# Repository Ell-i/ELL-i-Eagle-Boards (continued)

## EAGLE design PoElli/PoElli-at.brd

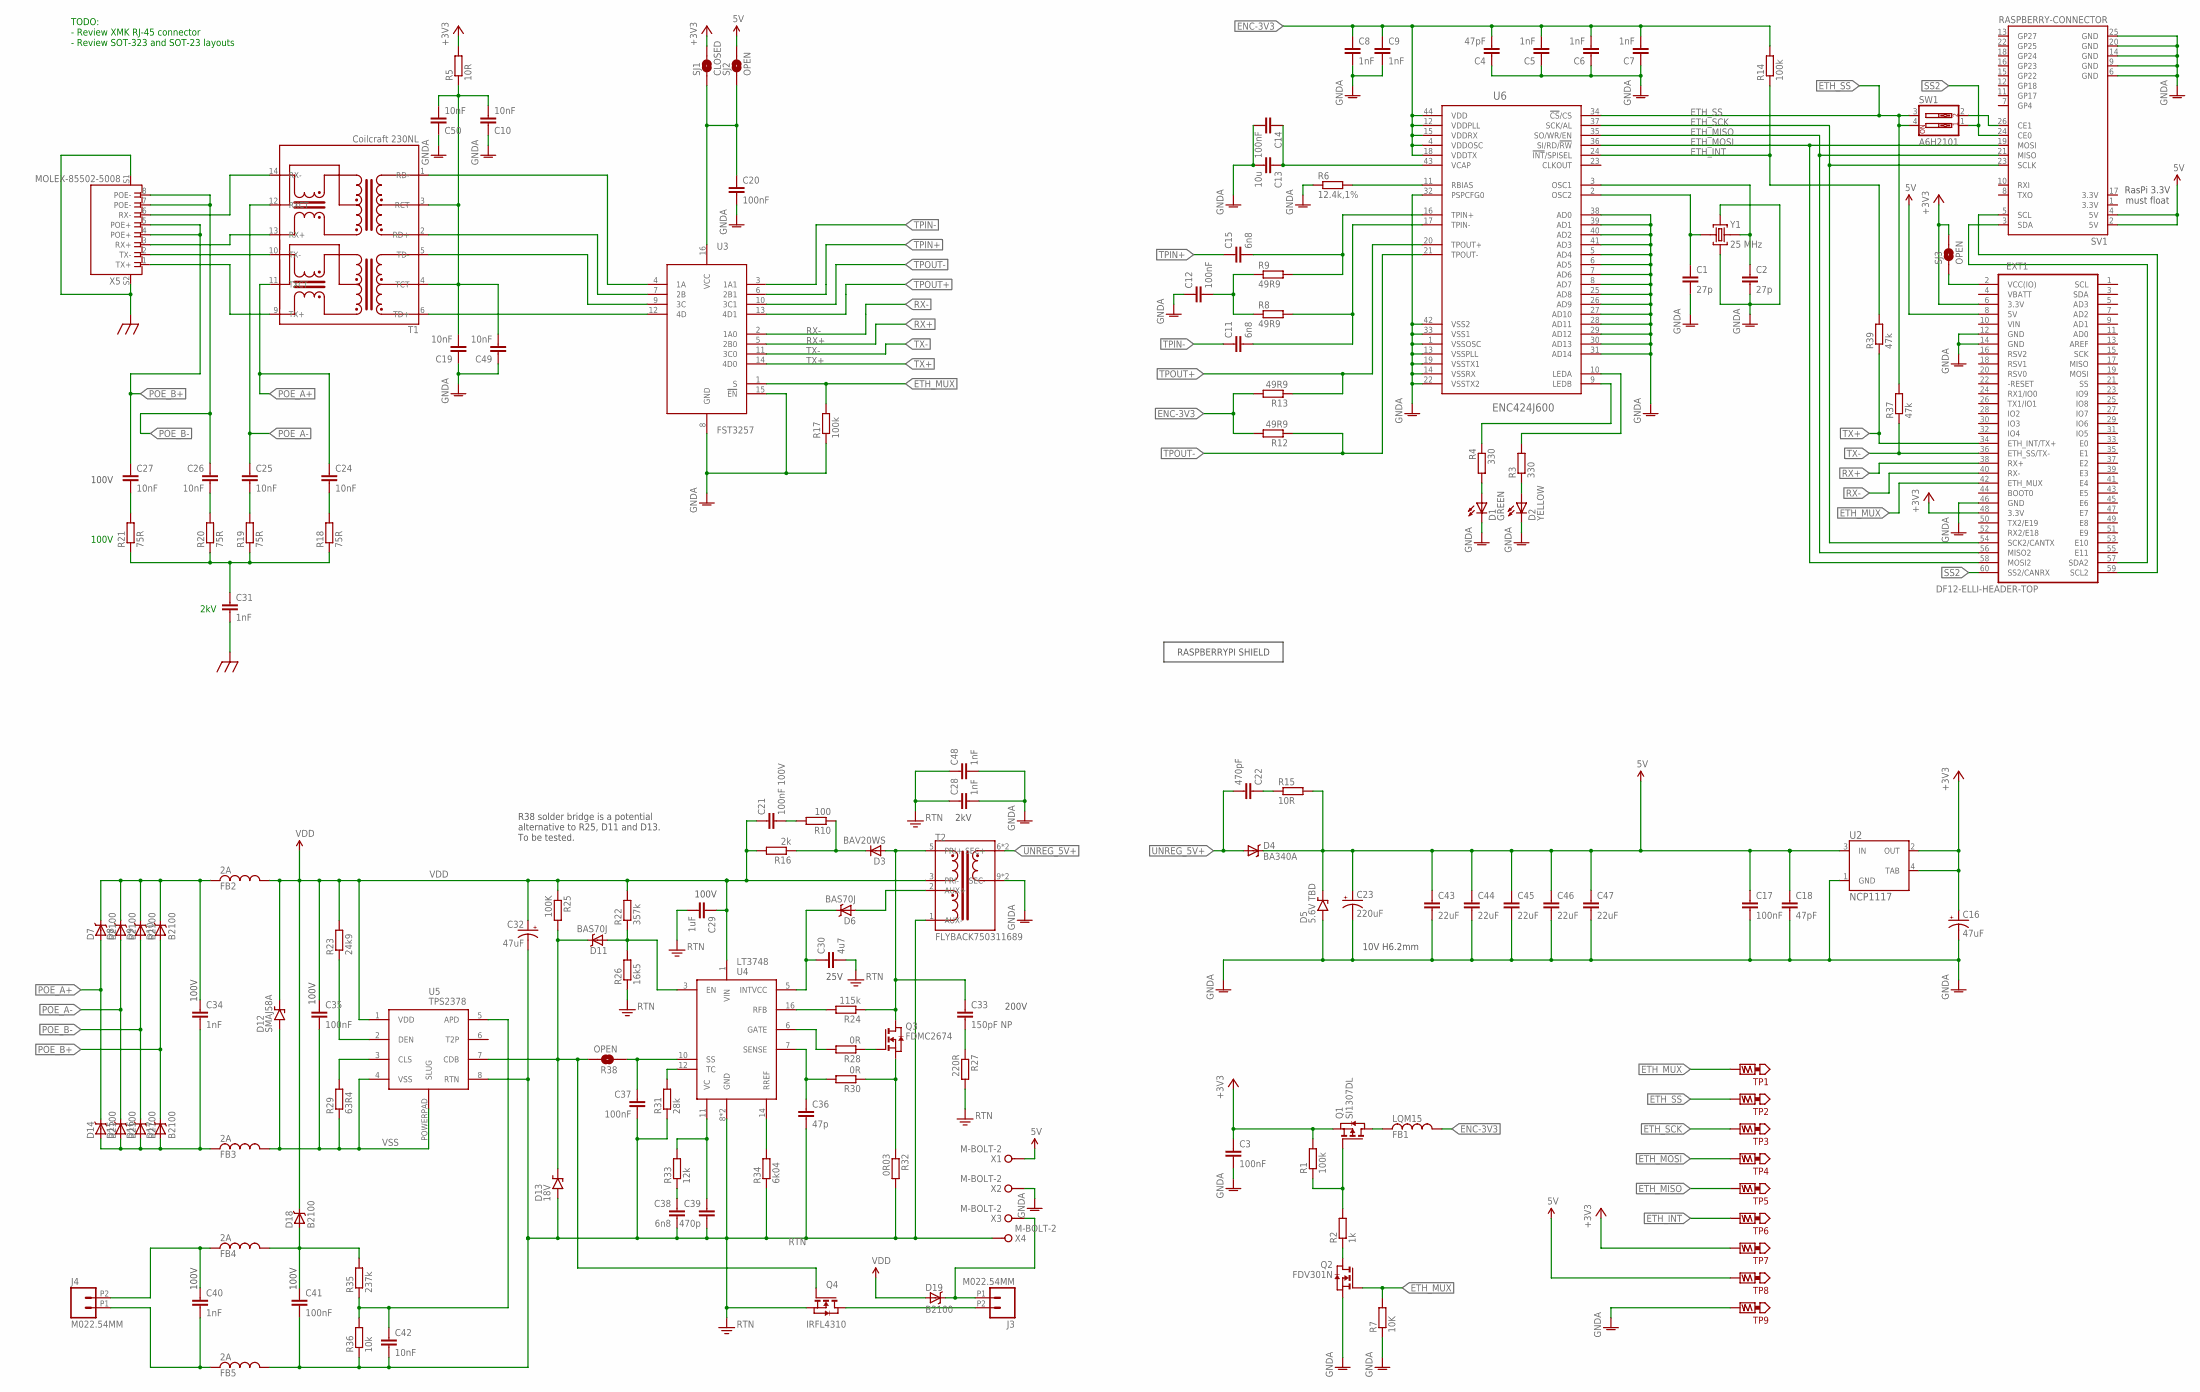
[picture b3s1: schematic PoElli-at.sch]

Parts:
C1, C2: 27p; C0402
C3, C12, C14, C17, C20, C37: 100nF; C0402
C4, C18: 47pF; C0402
C5, C6, C7, C8, C9: 1nF; C0402
C10, C19, C49, C50: 10nF; C0402
C11, C15, C38: 6n8; C0402
C13: 10u; C0603
C16, C32: 47uF; CT3216
C21: 100nF 100V; C0805
C22: 470pF; C0603
C23: 220uF; CPOL_PANASONIC_E
C24, C25, C26, C27, C42: 10nF; C0603
C28, C48: 1nF; C1206
C29: 1uF; C0805
C30: 4u7; C0805
C31: 1nF; C1210
C33: 150pF NP; C0805
C34, C40: 1nF; C0603
C35, C41: 100nF; C0805
C36: 47p; C0402
C39: 470p; C0402
C43, C44, C45, C46, C47: 22uF; C0805
D1: GREEN; LED-0603
D2: YELLOW; LED-0603
D3: BAV20WS; SOD-323
D4: BA340A; SMA-DIODE
D5: 5.6V TBD; SOD-123FL
D6, D11: BAS70J; SOD-323
D7, D8, D9, D10, D14, D15, D16, D17, D18, D19: B2100; DIODE-B2100
D12: SMAJ58A; SMA
D13: 18V; SOD-123FL
EXT1: DF12-ELLI-HEADER-TOP; DF12(4.0)-60DP-0.5V
FB1: LQM15; FB0402
FB2, FB3, FB4, FB5: 2A; FB1206
J3, J4: M022.54MM; 1X02_2.54_SCREWTERM
OUTLINE1: RASPBERRY-OUTLINE; RASPBERRYPI-SHIELD-OUTLINE
Q1: SI1307DL; SOT-323
Q2: FDV301N; SOT-23
Q3: FDMC2674; MLP8L33
Q4: IRFL4310; SOT223
R1, R14, R17: 100k; R0402
R2: 1k; R0402
R3, R4: 330; R0402
R5, R15: 10R; R0603
R6: 12.4k,1%; R0402
R7: 10K; R0402
R8, R9, R12, R13: 49R9; R0402
R10: 100; R0603
R16: 2k; R1206
R18, R19, R20, R21: 75R; R0603
R22: 357k; R0603
R23: 24k9; R0603
R24: 115k; R0603
R25: 100K; R0603
R26: 16k5; R0603
R27: 220R; R0805
R28, R30: 0R; R0603
R29: 63R4; R0805
R31: 28k; R0603
R32: 0R03; R0805
R33: 12k; R0603
R34: 6k04; R0603
R35: 237k; R0603
R36: 10k; R0603
R37, R39: 47k; R0805
R38: OPEN; SJ_2S-NO
SJ1: CLOSED; SJ_2S
SJ2, SJ3: OPEN; SJ_2S-NO
SV1: RASPBERRY-CONNECTOR; RASPBERRYPI-SHIELD-CONNECTOR
SW1: A6H2101; DIPSWITCH-02-50MIL
T1: Coilcraft 230NL; COILCRAFT-ETH1-230L
T2: FLYBACK750311689; WE_EP13_SMD_10PIN
TP1, TP5, TP6, TP7, TP8, TP9: TEST_POINT-5000; TP_5021
TP2, TP3, TP4: TEST_POINT-5021; TP_5000
U2: NCP1117; SOT223
U3: FST3257; SOIC-16-NARROW
U4: LT3748; MSOP16(12)
U5: TPS2378; SO08-POWERPAD
U6: ENC424J600; TQFP44-0.8MM
X1, X2, X3, X4: M-BOLT-2; M2-1
X5: MOLEX-85502-5008
Y1: 25 MHz; CRYSTAL-SMD-3225-GND

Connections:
3.3V: SV1.1 (3.3V), SV1.17 (3.3V)
5V: C17.1, C18.1, C23.+, C43.1, C44.1, C45.1, C46.1, C47.1, D4.C, D5.C, EXT1.8 (5V), R15.2, SJ2.2, SV1.2 (5V), SV1.4 (5V), TP8.P$1, U2.3 (IN), X1.1
+3V3: C3.1, C16.A (+), EXT1.6 (3.3V), EXT1.48 (3.3V), Q1.P$2 (S), R1.2, R5.2, SJ1.2, SJ3.2, TP7.P$1, U2.2 (OUT), U2.4 (TAB)
ENC-3V3: C4.2, C5.2, C6.2, C7.2, C8.1, C9.1, FB1.2, R12.2, R13.2, R14.2, U6.4 (VDDOSC), U6.12 (VDDPLL), U6.15 (VDDRX), U6.18 (VDDTX), U6.44 (VDD)
ETH_INT: R14.1, R39.2, TP6.P$1, U6.24 (!INT!/SPISEL)
ETH_MISO: EXT1.56 (MISO2), SV1.21 (MISO), TP5.P$1, U6.35 (SO/WR/EN)
ETH_MOSI: EXT1.58 (MOSI2), SV1.19 (MOSI), TP4.P$1, U6.36 (SI/RD/!RW)
ETH_MUX: EXT1.42 (ETH_MUX), Q2.P$1 (G), R7.2, R17.2, TP1.P$1, U3.1 (S)
ETH_SCK: EXT1.54 (SCK2/CANTX), SV1.23 (SCLK), TP3.P$1, U6.37 (SCK/AL)
ETH_SS: R37.2, SW1.3, SW1.4, TP2.P$1, U6.34 (!CS!/CS)
GNDA: C1.2, C2.2, C3.2, C4.1, C5.1, C6.1, C7.1, C8.2, C9.2, C10.1, C12.1, C13.2, C14.2, C16.C (-), C17.2, C18.2, C19.1, C20.2, C23.-, C28.2, C43.2, C44.2, C45.2, C46.2, C47.2, C48.2, C49.1, C50.1, D1.C, D2.C, D5.A, EXT1.12 (GND), EXT1.14 (GND), EXT1.46 (GND), Q2.P$2 (S), R6.1, R7.1, R17.1, SV1.6 (GND), SV1.9 (GND), SV1.14 (GND), SV1.20 (GND), SV1.25 (GND), T2.9 (SEC-), T2.10 (SEC-), TP9.P$1, U2.1 (GND), U3.8 (GND), U3.15 (!EN), U6.1 (VSSOSC), U6.5 (AD4), U6.6 (AD5), U6.7 (AD6), U6.8 (AD7), U6.13 (VSSPLL), U6.14 (VSSRX), U6.19 (VSSTX1), U6.22 (VSSTX2), U6.25 (AD8), U6.26 (AD9), U6.27 (AD10), U6.28 (AD11), U6.29 (AD12), U6.30 (AD13), U6.31 (AD14), U6.32 (PSPCFG0), U6.33 (VSS1), U6.38 (AD0), U6.39 (AD1), U6.40 (AD2), U6.41 (AD3), U6.42 (VSS2), X2.1, Y1.2 (GND), Y1.4 (GND)
unnamed: T1.10 (TX-), X5.2 (TX-)
unnamed: T1.9 (TX+), X5.1 (TX+)
unnamed: T1.13 (RX+), X5.3 (RX+)
unnamed: T1.14 (RX-), X5.6 (RX-)
unnamed: C31.1, R18.1, R19.1, R20.1, R21.1
unnamed: C34.1, D7.C, D8.C, D9.C, D10.C, FB2.1
unnamed: R31.2, U4.12 (TC)
unnamed: C34.2, D14.A, D15.A, D16.A, D17.A, FB3.1
unnamed: D11.2 (C), D13.C, Q4.1 (G), R25.2, R38.2, U5.7 (CDB)
unnamed: J3.P2 (2), Q4.2 (D), Q4.4 (D)
unnamed: T1.6 (TD+), U3.12 (4D)
unnamed: T1.5 (TD-), U3.9 (3C)
unnamed: T1.2 (RD+), U3.7 (2B)
unnamed: T1.1 (RD-), U3.4 (1A)
unnamed: C33.2, R27.1
unnamed: C22.1, R15.1
unnamed: D11.1 (A), R22.1, R26.2, U4.3 (EN)
unnamed: R23.1, U5.2 (DEN)
unnamed: R29.2, U5.3 (CLS)
unnamed: C37.1, R38.1, U4.10 (SS)
unnamed: D19.C, J3.P1 (1), X3.1
unnamed: C39.1, R33.2, U4.11 (VC)
unnamed: C38.1, R33.1
unnamed: R28.2, U4.6 (GATE)
unnamed: Q3.4 (G), R28.1
unnamed: C36.1, R30.2, U4.7 (SENSE)
unnamed: Q3.1 (S), Q3.2 (S), Q3.3 (S), R30.1, R32.1
unnamed: C33.1, D3.1 (A), Q3.5 (D), Q3.6 (D), Q3.7 (D), Q3.8 (D), Q3.F1 (D), R24.1, T2.5 (PRI+)
unnamed: D6.1 (A), T2.2 (AUX+)
unnamed: R24.2, U4.16 (RFB)
unnamed: R34.2, U4.14 (RREF)
unnamed: D3.2 (C), R10.1, R16.1
unnamed: C21.2, R10.2
unnamed: D1.A, R4.2
unnamed: C1.1, U6.2 (OSC2), Y1.1 (C1)
unnamed: D2.A, R3.1
unnamed: C11.2, R8.2, U6.17 (TPIN-)
unnamed: C10.2, C19.2, C49.2, C50.2, R5.1, T1.3 (RCT), T1.4 (TCT)
unnamed: R4.1, U6.9 (LEDB)
unnamed: R3.2, U6.10 (LEDA)
unnamed: C12.2, R8.1, R9.1
unnamed: R6.2, U6.11 (RBIAS)
unnamed: C2.1, U6.3 (OSC1), Y1.3 (C2)
unnamed: C27.2, R21.2
unnamed: C24.2, R18.2
unnamed: C25.2, R19.2
unnamed: C26.2, R20.2
unnamed: C40.1, FB4.1, J4.P2 (2)
unnamed: C42.1, R35.1, R36.2, U5.5 (APD)
unnamed: C40.2, FB5.1, J4.P1 (1)
unnamed: Q2.P$3 (D), R2.1
unnamed: Q1.P$1 (G), R1.1, R2.2
unnamed: C15.2, R9.2, U6.16 (TPIN+)
unnamed: FB1.1, Q1.P$3 (D)
unnamed: EXT1.57 (SDA2), SV1.3 (SDA)
unnamed: EXT1.59 (SCL2), SV1.5 (SCL)
unnamed: SV1.26 (CE1), SW1.2
unnamed: C41.1, D18.A, FB4.2, R35.2
POE_A+: C24.1, D7.A, D14.C, T1.11 (TXCT)
POE_A-: C25.1, D8.A, D15.C, T1.12 (RXCT)
POE_B+: C27.1, D10.A, D17.C, X5.4 (POE+), X5.5 (POE+)
POE_B-: C26.1, D9.A, D16.C, X5.7 (POE-), X5.8 (POE-)
RTN: C28.1, C29.2, C30.2, C32.C (-), C36.2, C37.2, C38.2, C39.2, C41.2, C42.2, C48.1, D13.A, FB5.2, Q4.3 (S), R26.1, R27.2, R31.1, R32.2, R34.1, R36.1, T2.1 (AUX-), U4.8 (GND), U4.9 (GND), U5.8 (RTN), X4.1
RX+: EXT1.38 (RX+), U3.5 (2B0)
RX-: EXT1.40 (RX-), U3.2 (1A0)
SGND: C31.2, X5.S1 (GND), X5.S2 (GND)
SS2: EXT1.60 (SS2/CANRX), SV1.24 (CE0), SW1.1
TPIN+: C15.1, U3.6 (2B1)
TPIN-: C11.1, U3.3 (1A1)
TPOUT+: R13.1, U3.13 (4D1), U6.20 (TPOUT+)
TPOUT-: R12.1, U3.10 (3C1), U6.21 (TPOUT-)
TX+: EXT1.34 (ETH_INT/TX+), R39.1, U3.14 (4D0)
TX-: EXT1.36 (ETH_SS/TX-), R37.1, U3.11 (3C0)
U3_VCC: C20.1, SJ1.1, SJ2.1, U3.16 (VCC)
U4_INTVCC: C30.1, D6.2 (C), U4.5 (INTVCC)
UNREG_5V+: C22.2, D4.A, T2.6 (SEC+), T2.7 (SEC+)
VBATT: EXT1.4 (VBATT)
VCAP: C13.1, C14.1, U6.43 (VCAP)
VCC(IO): EXT1.2 (VCC(IO)), SJ3.1
VDD: C21.1, C29.1, C32.A (+), C35.1, D12.1 (C), D18.C, D19.A, FB2.2, R16.2, R22.2, R23.2, R25.1, T2.3 (PRI-), U4.1 (VIN), U5.1 (VDD)
VIN: EXT1.10 (VIN)
VSS: C35.2, D12.2 (A), FB3.2, R29.1, U5.4 (VSS), U5.POWERPAD (SLUG)

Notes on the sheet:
2kV
100V
25V
RasPi 3.3V must float
R38 solder bridge is a potential alternative to R25, D11 and D13. To be tested.
200V
10V H6.2mm
TODO: - Review XMK RJ-45 connector - Review SOT-323 and SOT-23 layouts

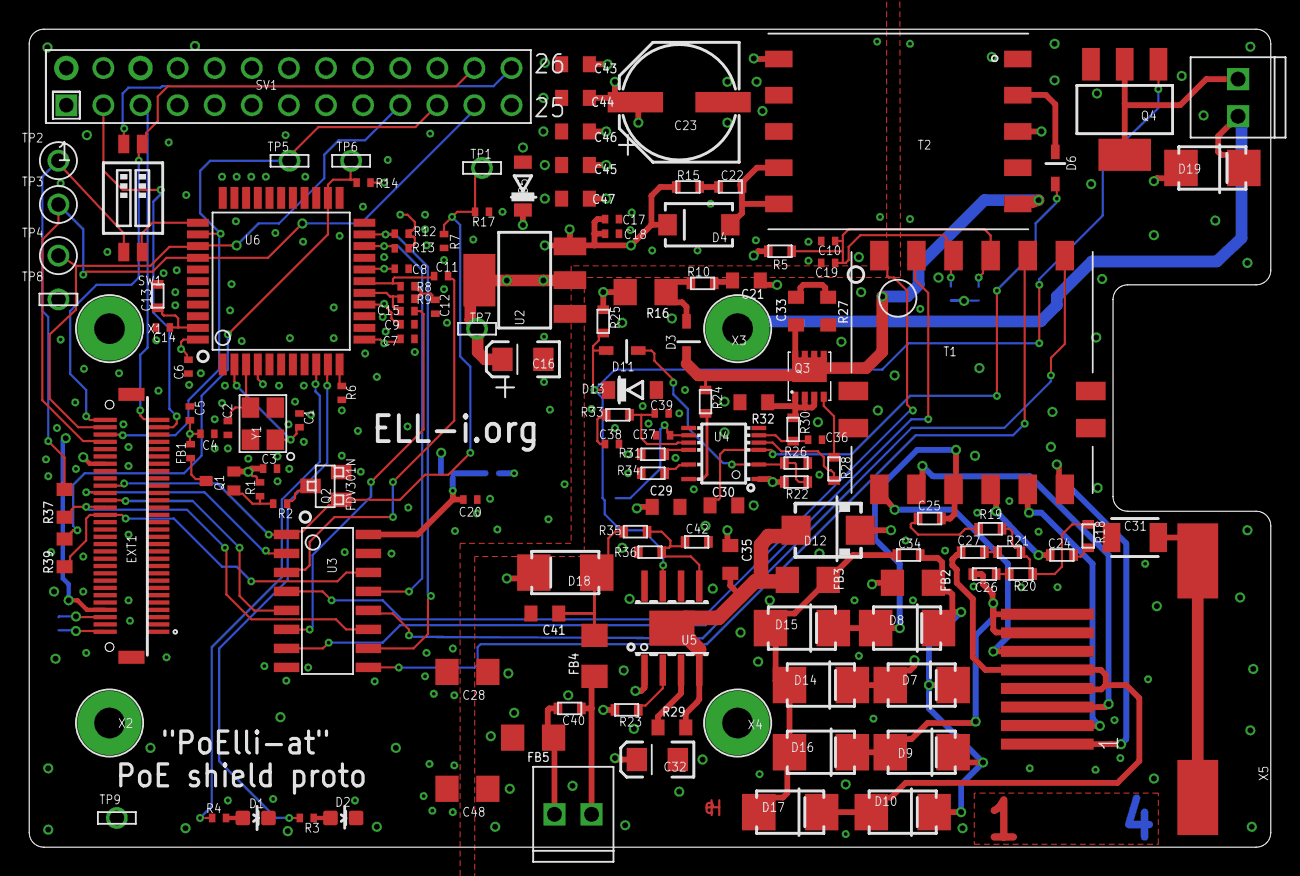
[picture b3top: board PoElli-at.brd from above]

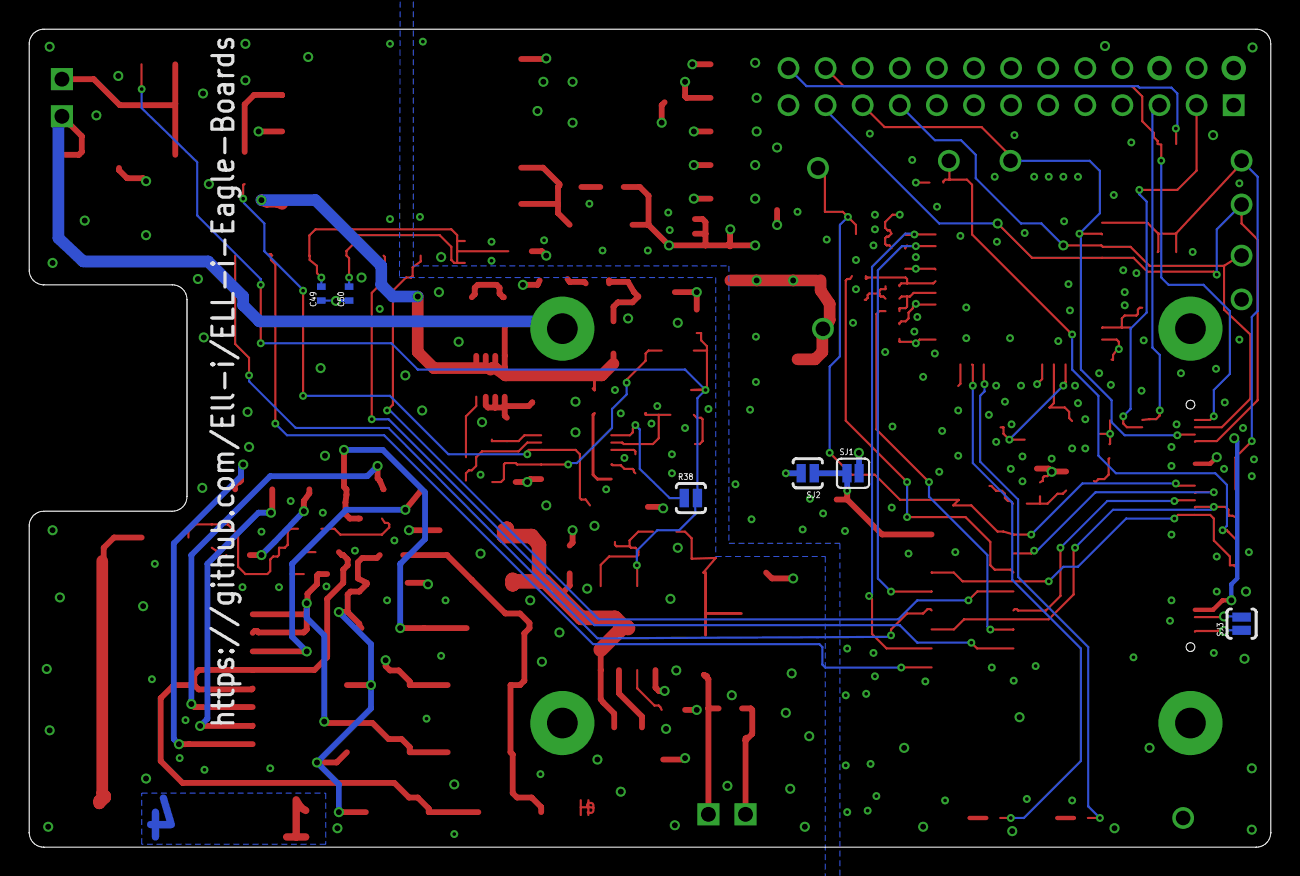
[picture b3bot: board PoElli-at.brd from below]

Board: 4 copper layers, 85.0 x 56.0 mm, 148 parts (6 on the bottom side), 91 nets.

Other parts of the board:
U$3: EH-LOGO

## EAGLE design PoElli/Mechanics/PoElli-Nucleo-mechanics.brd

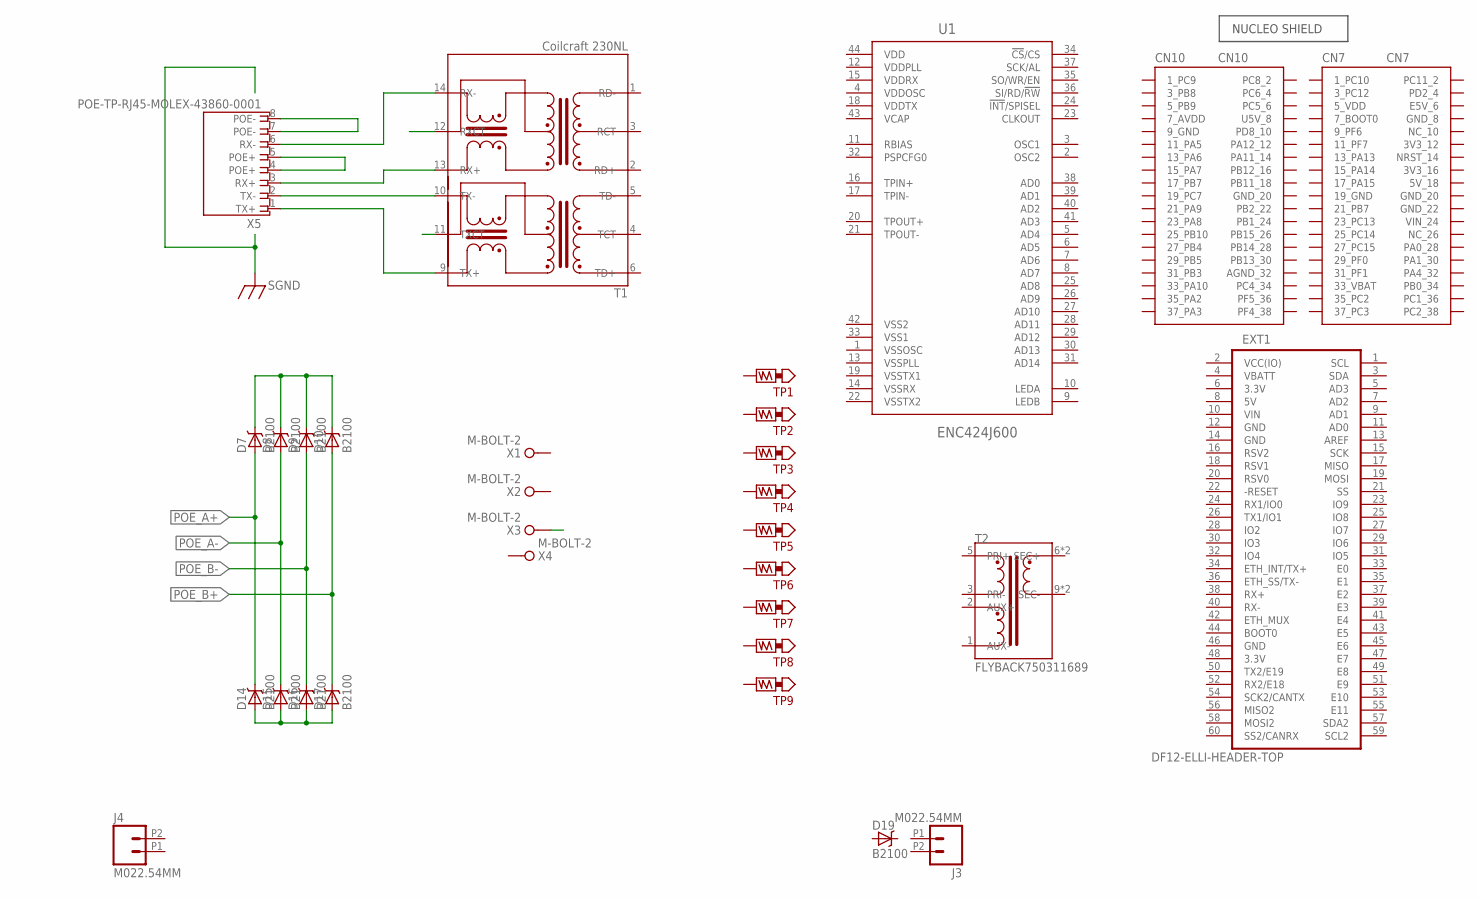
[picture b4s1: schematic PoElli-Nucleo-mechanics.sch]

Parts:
CN7: NUCLEO-CN7; NUCLEO-HEADER
CN10: NUCLEO-CN10; NUCLEO-HEADER
D7, D8, D9, D10, D14, D15, D16, D17, D19: B2100; DIODE-B2100
EXT1: DF12-ELLI-HEADER-TOP; DF12(4.0)-60DP-0.5V
J3, J4: M022.54MM; 1X02_2.54_SCREWTERM
NUCLEO: NUCLEO-SHIELD-OUTLINE-EXTENDED; NUCLEO-SHIELD-UNDERSIDE-EXTENDED-OUTLINE
T1: Coilcraft 230NL; COILCRAFT-ETH1-230L
T2: FLYBACK750311689; WE_EP13_SMD_10PIN
TP1, TP5, TP6, TP7, TP8, TP9: TEST_POINT-5000; TP_5021
TP2, TP3, TP4: TEST_POINT-5021; TP_5000
U1: ENC424J600; TQFP44-0.8MM
X1, X2, X3, X4: M-BOLT-2; M2-1
X5: POE-TP-RJ45-MOLEX-43860-0001; MOLEX-43860-0001

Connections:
3.3V: EXT1.6 (3.3V)
5V: EXT1.8 (5V)
GND: EXT1.12 (GND), EXT1.14 (GND)
unnamed: T1.10 (TX-), X5.2 (TX-)
unnamed: T1.9 (TX+), X5.1 (TX+)
unnamed: T1.13 (RX+), X5.3 (RX+)
unnamed: T1.14 (RX-), X5.6 (RX-)
unnamed: D7.C, D8.C, D9.C, D10.C
unnamed: D14.A, D15.A, D16.A, D17.A
unnamed: X5.7 (POE-), X5.8 (POE-)
POE_A+: D7.A, D14.C
POE_A-: D8.A, D15.C, T1.12 (RXCT)
POE_B+: D10.A, D17.C, X5.4 (POE+), X5.5 (POE+)
POE_B-: D9.A, D16.C
VBATT: EXT1.4 (VBATT)
VCAP: U1.43 (VCAP)
VCC(IO): EXT1.2 (VCC(IO))
VDD: U1.44 (VDD)
VDDOSC: U1.4 (VDDOSC)
VDDPLL: U1.12 (VDDPLL)
VDDRX: U1.15 (VDDRX)
VDDTX: U1.18 (VDDTX)
VIN: EXT1.10 (VIN)
VSS1: U1.33 (VSS1)
VSS2: U1.42 (VSS2)
VSSOSC: U1.1 (VSSOSC)
VSSPLL: U1.13 (VSSPLL)
VSSRX: U1.14 (VSSRX)
VSSTX1: U1.19 (VSSTX1)
VSSTX2: U1.22 (VSSTX2)

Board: 2 copper layers, 32 parts (1 on the bottom side), 12 nets, no tracks yet.

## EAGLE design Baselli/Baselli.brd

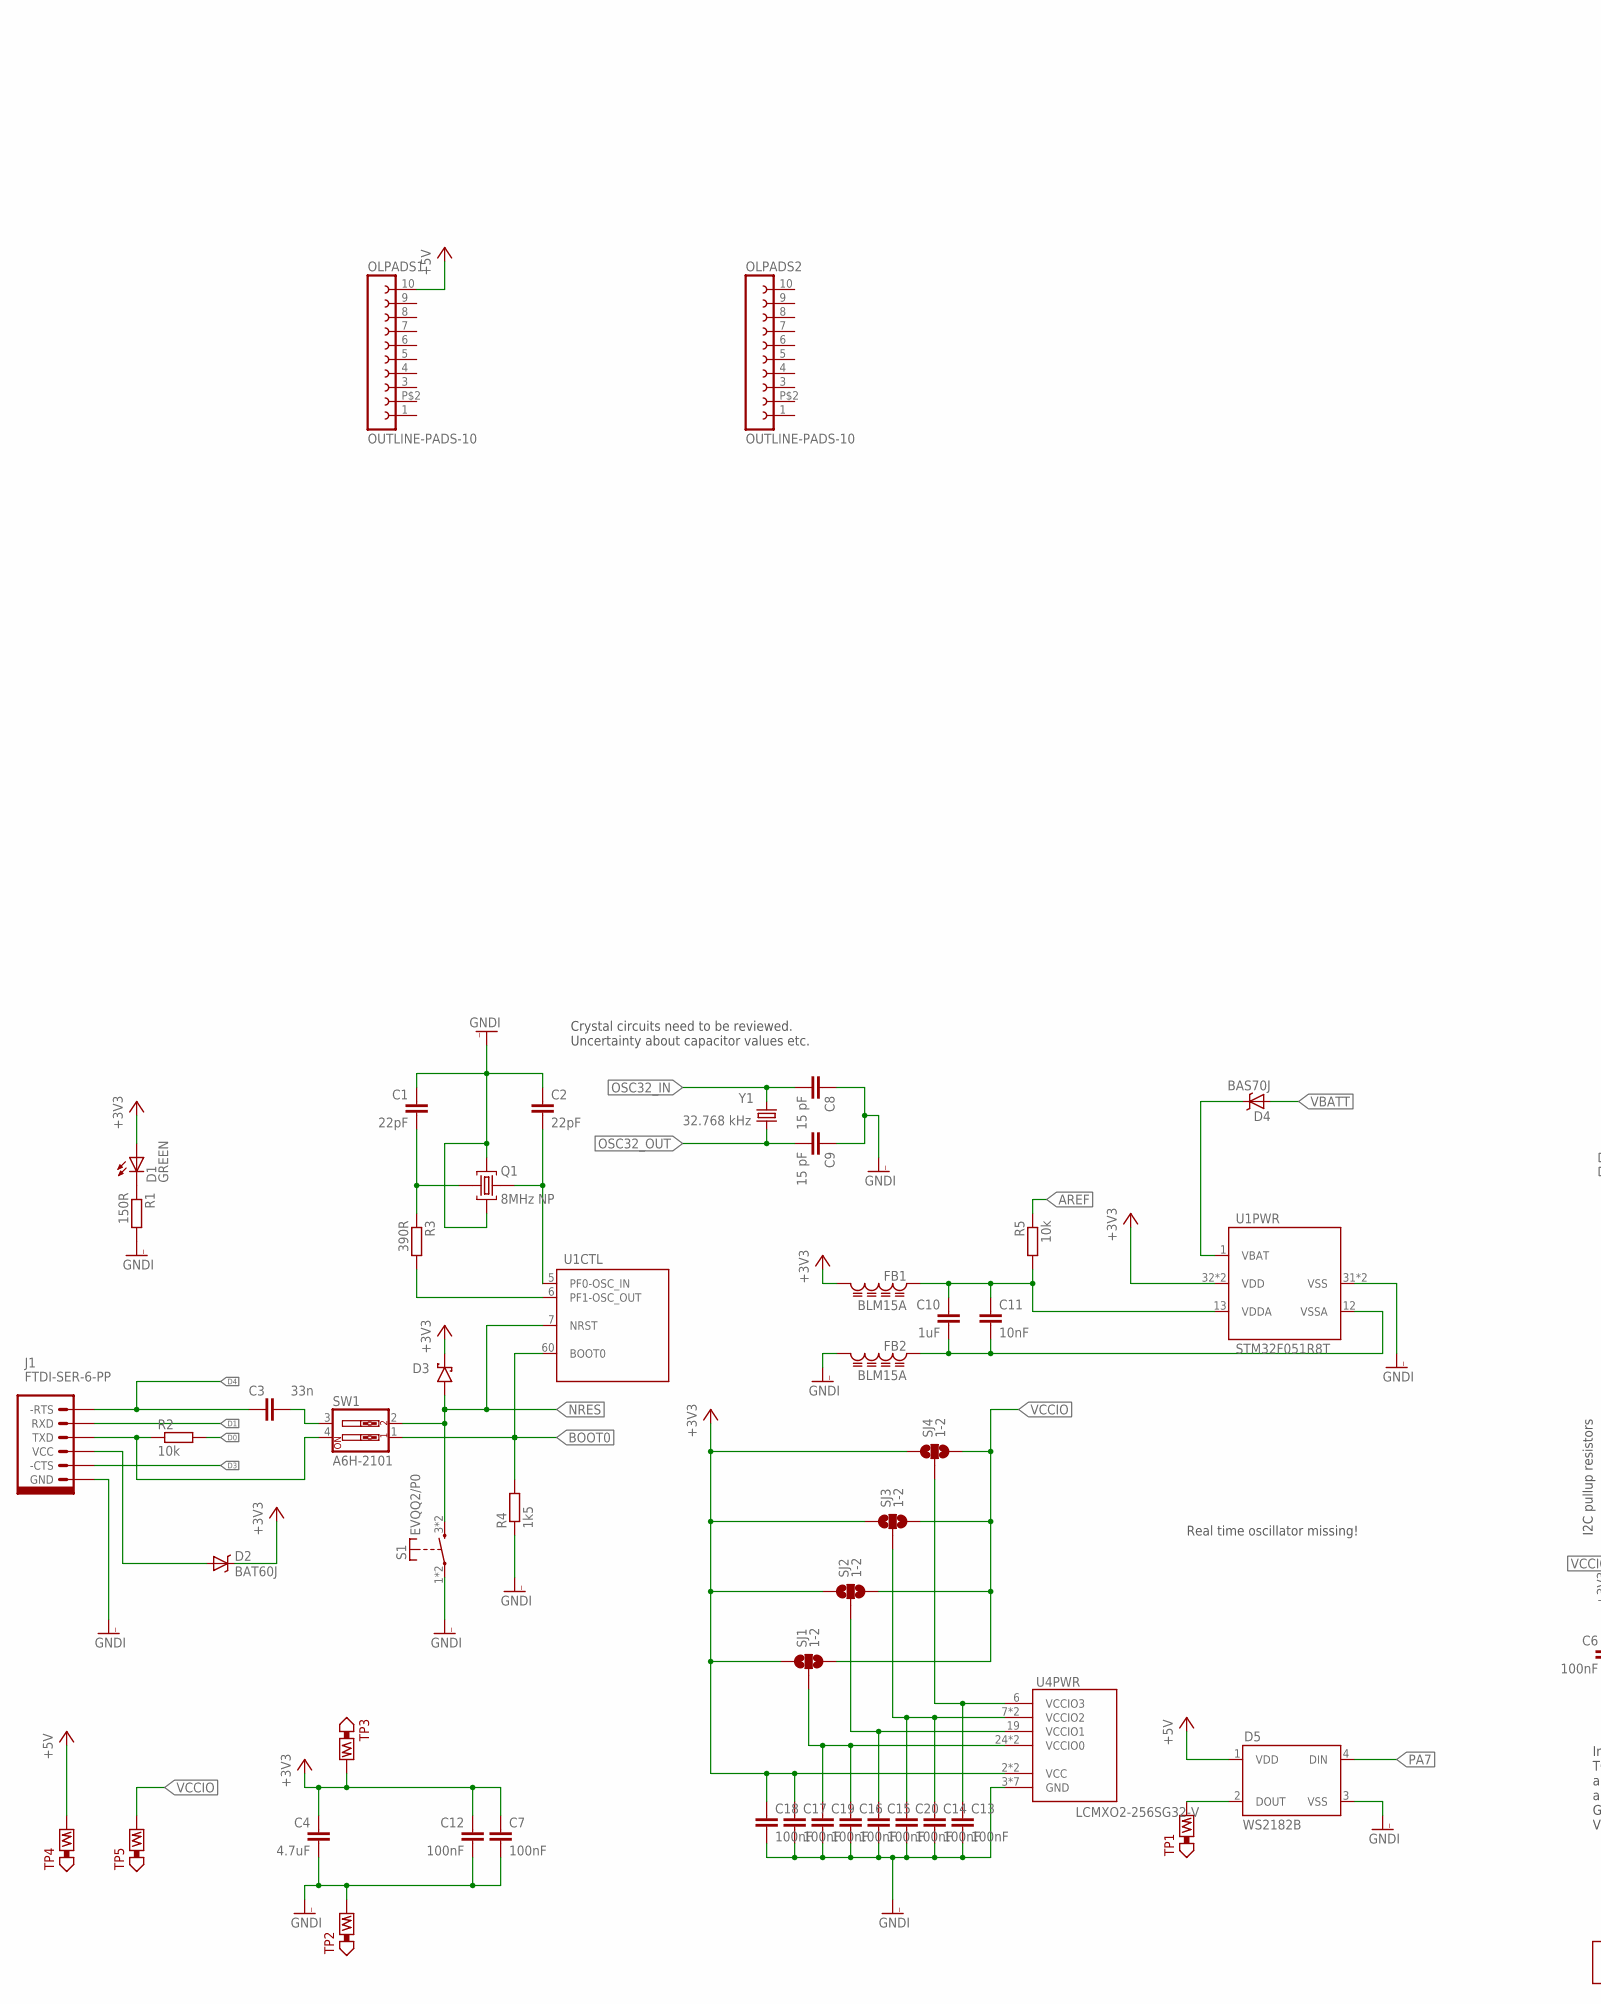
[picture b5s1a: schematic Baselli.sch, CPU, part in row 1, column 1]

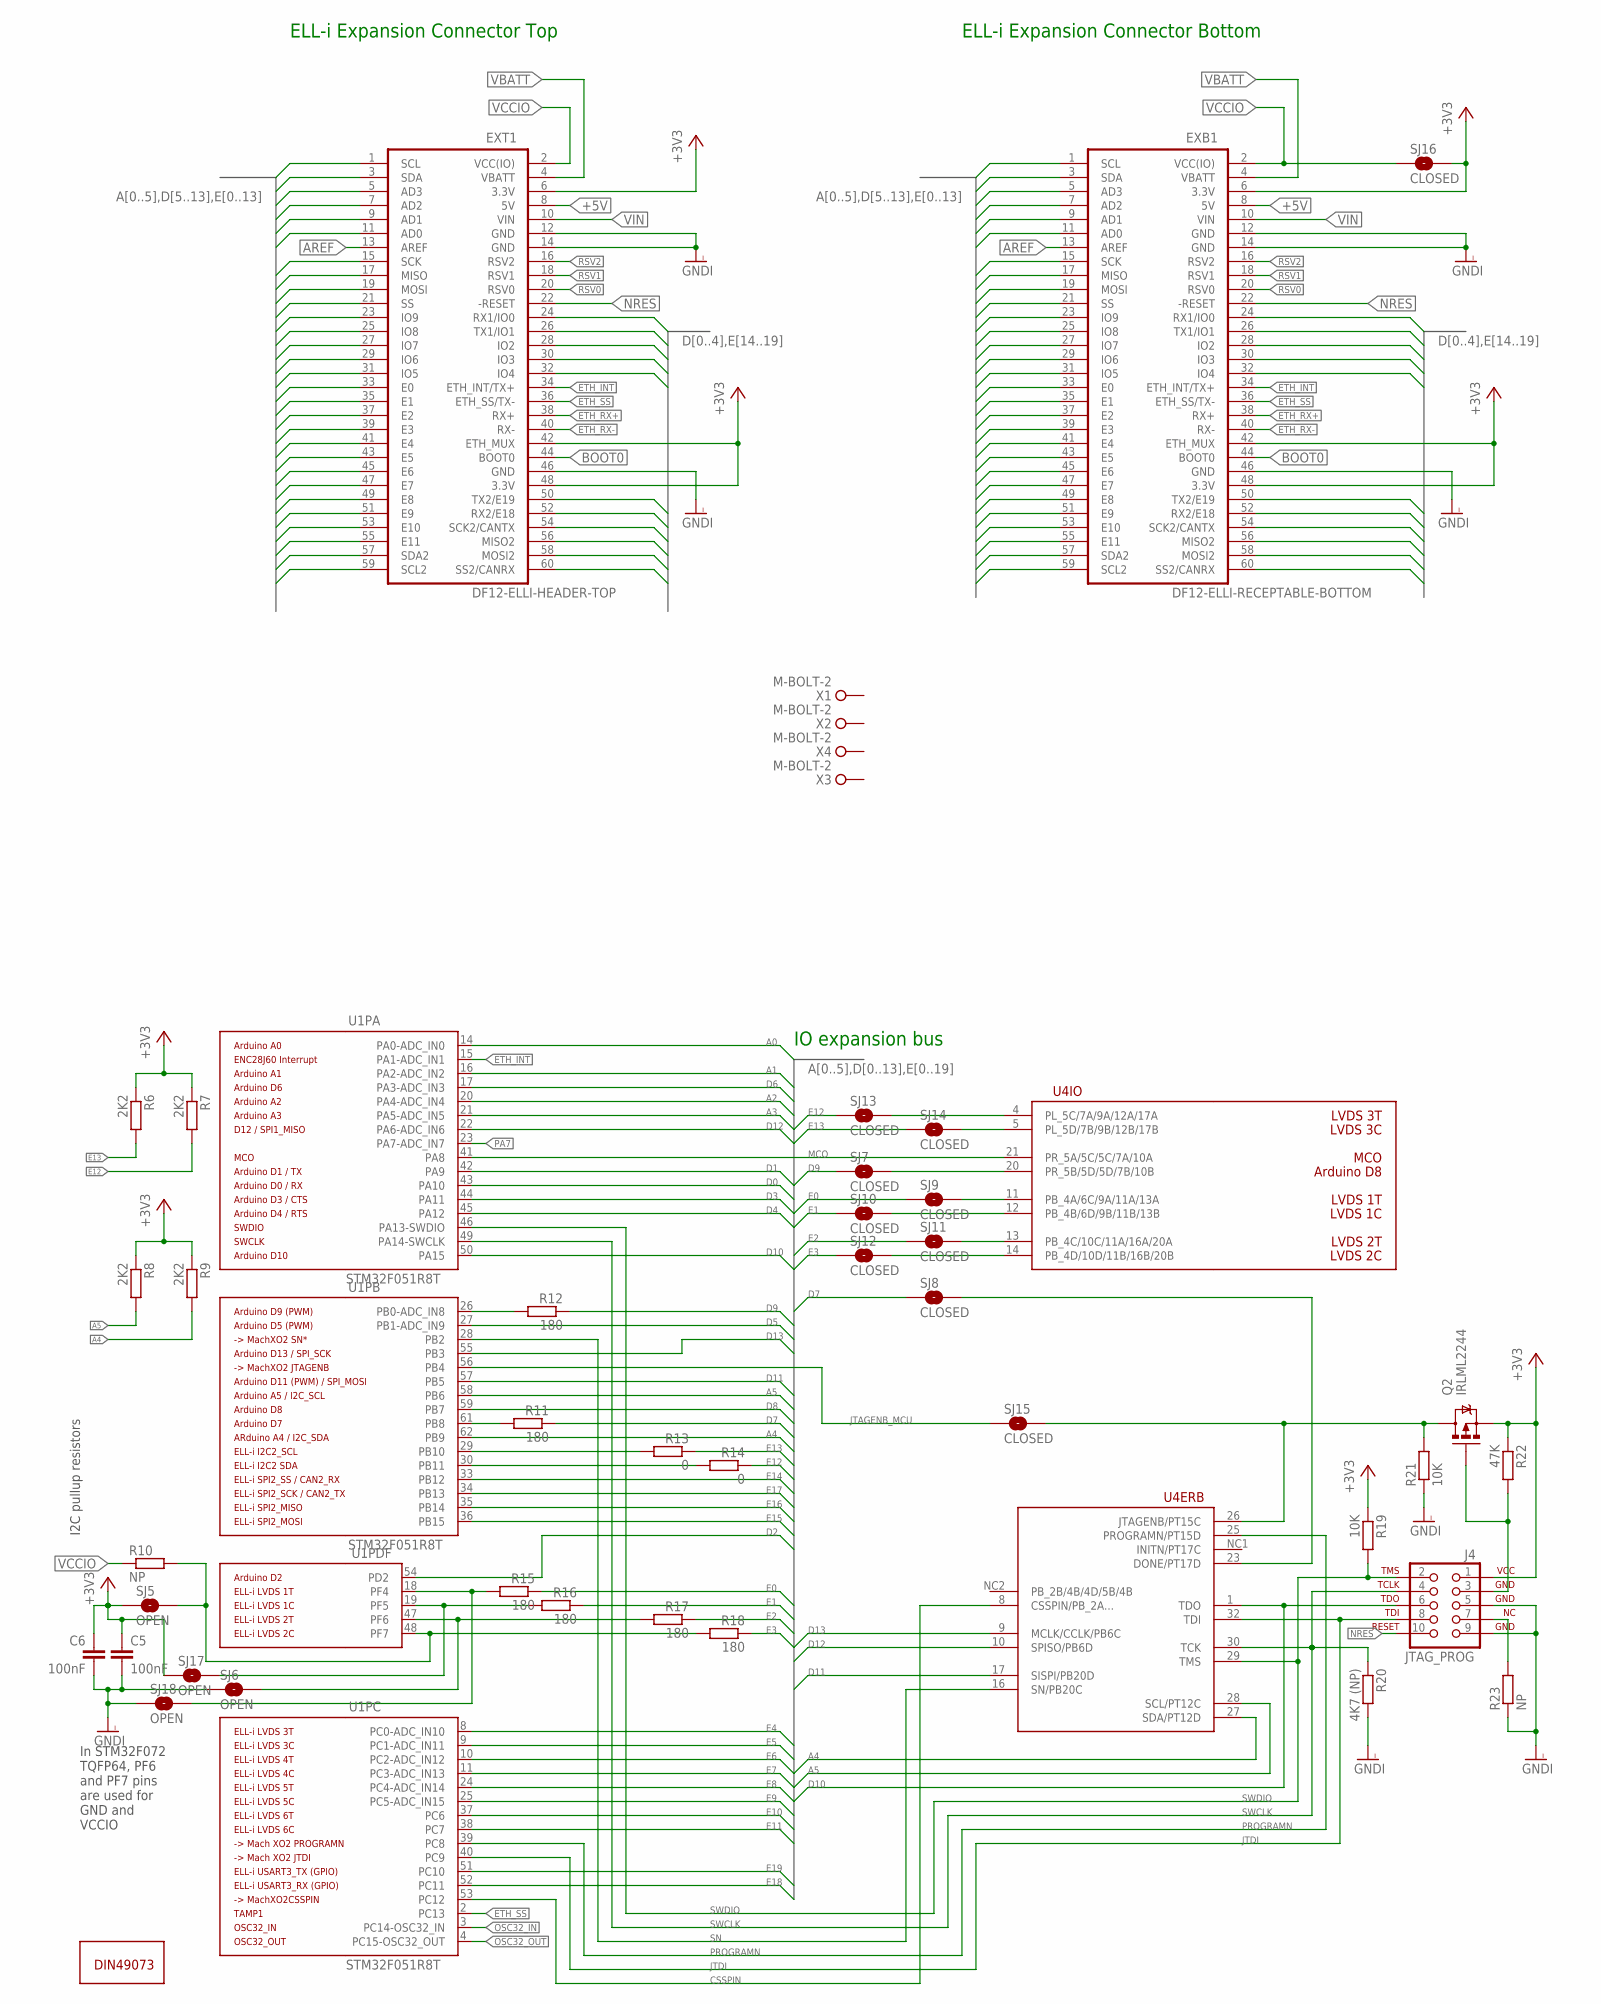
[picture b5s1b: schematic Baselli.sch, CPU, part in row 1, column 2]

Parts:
C1, C2: 22pF; C0402
C3: 33n; C0402
C4: 4.7uF; C0402
C5, C6, C7, C12, C13, C14, C15, C16, C17, C18, C19, C20: 100nF; C0402
C8, C9: 15 pF; C0402
C10: 1uF; C0402
C11: 10nF; C0402
D1: GREEN; LED-0603
D2: BAT60J; SOD-323
D3: BAT60J; SOD323_DIODE
D4: BAS70J; SOD-323
D5: WS2182B; WS2812B
DIMENSIONS1: DIN49073-OUTLINE; DIN49073-1:2010-02-OUTLINE
EXB1: DF12-ELLI-RECEPTABLE-BOTTOM; DF12-60DS-0.5V
EXT1: DF12-ELLI-HEADER-TOP; DF12(4.0)-60DP-0.5V
FB1, FB2: BLM15A; 0402
J1: FTDI-SER-6-PP; FTDI-SER-6-SIL
J4: JTAG_PROG; CLP-105-02-X-D
OLPADS1, OLPADS2: OUTLINE-PADS-10; DIN49073-1:2010-02-PADS-10
Q1: 8MHz NP; CRYSTAL-SMD-3225-GND
Q2: IRLML2244; SOT23-3
R1: 150R; R0402
R2: 10k; R0402
R3: 390R; R0402
R4: 1k5; R0402
R5: 10k; R0805
R6, R7, R8, R9: 2K2; R0402
R10, R23: NP; R0805
R11, R12, R15, R16, R17, R18: 180; R0805
R13, R14: 0; R0805
R19, R21: 10K; R0402
R20: 4K7 (NP); R0603
R22: 47K; R0402
S1: EVQQ2/P0
SJ1, SJ2, SJ3, SJ4: 1-2; SJ_3_PASTE1&2
SJ5, SJ6, SJ17, SJ18: OPEN; SJ_2S-NO
SJ7, SJ8, SJ9, SJ10, SJ11, SJ12, SJ13, SJ14, SJ15, SJ16: CLOSED; SJ_2S-TRACE
SW1: A6H-2101; DIPSWITCH-02-50MIL
TP1, TP2, TP3, TP4, TP5: TEST_POINT-5000; TP_5021
U1: STM32F051R8T; LQFP64
U4: LCMXO2-256SG32-V; QFN-32-PAD-VIAS
X1, X2, X3, X4: M-BOLT-2; M2-1
Y1: 32.768 kHz; CRYSTAL-32KHZ-SMD

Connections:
+3V3: C4.1, C5.1, C6.1, C7.1, C12.1, C17.1, C18.1, D1.A, D2.C, D3.1 (C), EXB1.6 (3.3V), EXB1.42 (ETH_MUX), EXB1.48 (3.3V), EXT1.6 (3.3V), EXT1.42 (ETH_MUX), EXT1.48 (3.3V), FB1.2, J4.1, Q2.2 (S), R6.1, R7.1, R8.1, R9.1, R19.1, R22.1, SJ1.1, SJ2.1, SJ3.1, SJ4.1, SJ5.1, SJ16.2, SJ17.1, TP3.P$1, U1.32 (VDD), U1.64 (VDD), U4.2 (VCC), U4.18 (VCC)
+5V: D5.1 (VDD), EXB1.8 (5V), EXT1.8 (5V), OLPADS1.10, TP4.P$1
-RTS: C3.2, SW1.3
A0: EXB1.11 (AD0), EXT1.11 (AD0), U1.14 (PA0-ADC_IN0)
A1: EXB1.9 (AD1), EXT1.9 (AD1), U1.16 (PA2-ADC_IN2)
A2: EXB1.7 (AD2), EXT1.7 (AD2), U1.20 (PA4-ADC_IN4)
A3: EXB1.5 (AD3), EXT1.5 (AD3), U1.21 (PA5-ADC_IN5)
A4: EXB1.3 (SDA), EXT1.3 (SDA), R9.2, U1.62 (PB9), U4.27 (SDA/PT12D)
A5: EXB1.1 (SCL), EXT1.1 (SCL), R8.2, U1.58 (PB6), U4.28 (SCL/PT12C)
AREF: EXB1.13 (AREF), EXT1.13 (AREF), R5.1
BOOT0: EXB1.44 (BOOT0), EXT1.44 (BOOT0), R4.2, SW1.1, U1.60 (BOOT0)
BOOT0TX: J1.TXD, R2.1, SW1.4
CSSPIN: U1.53 (PC12), U4.8 (CSSPIN/PB_2A...)
D0: EXB1.24 (RX1/IO0), EXT1.24 (RX1/IO0), R2.2, U1.43 (PA10)
D1: EXB1.26 (TX1/IO1), EXT1.26 (TX1/IO1), J1.RXD, U1.42 (PA9)
D2: EXB1.28 (IO2), EXT1.28 (IO2), U1.54 (PD2)
D3: EXB1.30 (IO3), EXT1.30 (IO3), J1.-CTS, U1.44 (PA11)
D4: C3.1, EXB1.32 (IO4), EXT1.32 (IO4), J1.-RTS, U1.45 (PA12)
D5: EXB1.31 (IO5), EXT1.31 (IO5), U1.27 (PB1-ADC_IN9)
D6: EXB1.29 (IO6), EXT1.29 (IO6), U1.17 (PA3-ADC_IN3)
D7: EXB1.27 (IO7), EXT1.27 (IO7), R11.1, SJ8.1
D8: EXB1.25 (IO8), EXT1.25 (IO8), U1.59 (PB7)
D9: EXB1.23 (IO9), EXT1.23 (IO9), R12.1, SJ7.1
D10: EXB1.21 (SS), EXT1.21 (SS), J4.6, U1.50 (PA15), U4.1 (TDO)
D11: EXB1.19 (MOSI), EXT1.19 (MOSI), U1.57 (PB5), U4.17 (SISPI/PB20D)
D12: EXB1.17 (MISO), EXT1.17 (MISO), U1.22 (PA6-ADC_IN6), U4.10 (SPISO/PB6D)
D13: EXB1.15 (SCK), EXT1.15 (SCK), U1.55 (PB3), U4.9 (MCLK/CCLK/PB6C)
DONE: SJ8.2, U4.23 (DONE/PT17D)
DOUT: D5.2 (DOUT), TP1.P$1
E0: EXB1.33 (E0), EXT1.33 (E0), R15.1, SJ9.1
E1: EXB1.35 (E1), EXT1.35 (E1), R16.1, SJ10.1
E2: EXB1.37 (E2), EXT1.37 (E2), R17.1, SJ11.1
E3: EXB1.39 (E3), EXT1.39 (E3), R18.1, SJ12.1
E4: EXB1.41 (E4), EXT1.41 (E4), U1.8 (PC0-ADC_IN10)
E5: EXB1.43 (E5), EXT1.43 (E5), U1.9 (PC1-ADC_IN11)
E6: EXB1.45 (E6), EXT1.45 (E6), U1.10 (PC2-ADC_IN12)
E7: EXB1.47 (E7), EXT1.47 (E7), U1.11 (PC3-ADC_IN13)
E8: EXB1.49 (E8), EXT1.49 (E8), U1.24 (PC4-ADC_IN14)
E9: EXB1.51 (E9), EXT1.51 (E9), U1.25 (PC5-ADC_IN15)
E10: EXB1.53 (E10), EXT1.53 (E10), U1.37 (PC6)
E11: EXB1.55 (E11), EXT1.55 (E11), U1.38 (PC7)
E12: EXB1.57 (SDA2), EXT1.57 (SDA2), R7.2, R14.1, SJ13.1
E13: EXB1.59 (SCL2), EXT1.59 (SCL2), R6.2, R13.1, SJ14.1
E14: EXB1.60 (SS2/CANRX), EXT1.60 (SS2/CANRX), U1.33 (PB12)
E15: EXB1.58 (MOSI2), EXT1.58 (MOSI2), U1.36 (PB15)
E16: EXB1.56 (MISO2), EXT1.56 (MISO2), U1.35 (PB14)
E17: EXB1.54 (SCK2/CANTX), EXT1.54 (SCK2/CANTX), U1.34 (PB13)
E18: EXB1.52 (RX2/E18), EXT1.52 (RX2/E18), U1.52 (PC11)
E19: EXB1.50 (TX2/E19), EXT1.50 (TX2/E19), U1.51 (PC10)
ETH_INT: EXB1.34 (ETH_INT/TX+), EXT1.34 (ETH_INT/TX+), U1.15 (PA1-ADC_IN1)
ETH_RX+: EXB1.38 (RX+), EXT1.38 (RX+)
ETH_RX-: EXB1.40 (RX-), EXT1.40 (RX-)
ETH_SS: EXB1.36 (ETH_SS/TX-), EXT1.36 (ETH_SS/TX-), U1.2 (PC13)
GNDI: C1.1, C2.1, C4.2, C5.2, C6.2, C7.2, C8.1, C9.1, C12.2, C13.2, C14.2, C15.2, C16.2, C17.2, C18.2, C19.2, C20.2, D5.3 (VSS), EXB1.12 (GND), EXB1.14 (GND), EXB1.46 (GND), EXT1.12 (GND), EXT1.14 (GND), EXT1.46 (GND), FB2.2, J1.GND, J4.5, J4.9, Q1.2 (GND), Q1.4 (GND), R1.2, R4.1, R20.2, R21.1, R23.1, S1.1, S1.2, SJ6.1, SJ18.1, TP2.P$1, U1.31 (VSS), U1.63 (VSS), U4.3 (GND), U4.22 (GND), U4.EP (GND), U4.VIA1 (GND), U4.VIA2 (GND), U4.VIA3 (GND), U4.VIA4 (GND)
JTAGENB: Q2.3 (D), R21.2, SJ15.2, U4.26 (JTAGENB/PT15C)
JTAGENB_MCU: SJ15.1, U1.56 (PB4)
JTAGEN_GATE: J4.3, Q2.1 (G), R22.2
JTDI: J4.8, U1.40 (PC9), U4.32 (TDI)
MCO: U1.41 (PA8), U4.21 (PR_5A/5C/5C/7A/10A)
N41567: D1.C, R1.1
N205481: C1.2, Q1.1 (C1), R3.1
unnamed: R11.2, U1.61 (PB8)
unnamed: J4.7, R23.2
unnamed: R12.2, U1.26 (PB0-ADC_IN8)
unnamed: SJ9.2, U4.11 (PB_4A/6C/9A/11A/13A)
unnamed: SJ10.2, U4.12 (PB_4B/6D/9B/11B/13B)
unnamed: SJ7.2, U4.20 (PR_5B/5D/5D/7B/10B)
unnamed: SJ11.2, U4.13 (PB_4C/10C/11A/16A/20A)
unnamed: SJ12.2, U4.14 (PB_4D/10D/11B/16B/20B)
unnamed: SJ13.2, U4.4 (PL_5C/7A/9A/12A/17A)
unnamed: SJ14.2, U4.5 (PL_5D/7B/9B/12B/17B)
NRES: D3.2 (A), EXB1.22 (-RESET), EXT1.22 (-RESET), J4.10, S1.3 (S), S1.4 (S), SW1.2, U1.7 (NRST)
OSC32_IN: C8.2, U1.3 (PC14-OSC32_IN), Y1.X2 (2)
OSC32_OUT: C9.2, U1.4 (PC15-OSC32_OUT), Y1.X1 (1)
PA7: D5.4 (DIN), U1.23 (PA7-ADC_IN7)
PB10: R13.2, U1.29 (PB10)
PB11: R14.2, U1.30 (PB11)
PF0: C2.2, Q1.3 (C2), U1.5 (PF0-OSC_IN)
PF1: R3.2, U1.6 (PF1-OSC_OUT)
PF4: R15.2, SJ18.2, U1.18 (PF4)
PF5: R16.2, SJ17.2, U1.19 (PF5)
PF6: R17.2, SJ6.2, U1.47 (PF6)
PF7: R10.2, R18.2, SJ5.2, U1.48 (PF7)
PROGRAMN: U1.39 (PC8), U4.25 (PROGRAMN/PT15D)
RSV0: EXB1.20 (RSV0), EXT1.20 (RSV0)
RSV1: EXB1.18 (RSV1), EXT1.18 (RSV1)
RSV2: EXB1.16 (RSV2), EXT1.16 (RSV2)
SN: U1.28 (PB2), U4.16 (SN/PB20C)
SWCLK: J4.4, R20.1, U1.49 (PA14-SWCLK), U4.30 (TCK)
SWDIO: J4.2, R19.2, U1.46 (PA13-SWDIO), U4.29 (TMS)
VBAT: D4.2 (C), U1.1 (VBAT)
VBATT: D4.1 (A), EXB1.4 (VBATT), EXT1.4 (VBATT)
VCC-IN: D2.A, J1.VCC
VCCIO: EXB1.2 (VCC(IO)), EXT1.2 (VCC(IO)), R10.1, SJ1.3, SJ2.3, SJ3.3, SJ4.3, SJ16.1, TP5.P$1
VCCIO0: C16.1, C19.1, SJ1.2, U4.24 (VCCIO0), U4.31 (VCCIO0)
VCCIO1: C15.1, SJ2.2, U4.19 (VCCIO1)
VCCIO2: C14.1, C20.1, SJ3.2, U4.7 (VCCIO2), U4.15 (VCCIO2)
VCCIO3: C13.1, SJ4.2, U4.6 (VCCIO3)
VDDA: C10.1, C11.1, FB1.1, R5.2, U1.13 (VDDA)
VIN: EXB1.10 (VIN), EXT1.10 (VIN)
VSSA: C10.2, C11.2, FB2.1, U1.12 (VSSA)

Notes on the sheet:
IO expansion bus
ELL-i Expansion Connector Top
ELL-i Expansion Connector Bottom
In STM32F072 TQFP64, PF6 and PF7 pins are used for GND and VCCIO
Crystal circuits need to be reviewed. Uncertainty about capacitor values etc.
I2C pullup resistors
Real time oscillator missing!
